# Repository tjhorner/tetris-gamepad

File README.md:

# Tetris Gamepad

These are the source files for an arcade-style gamepad designed for Tetris gameplay. Work in progress (things will break!)

**Disclaimer**: Tetris is a trademark of The Tetris Company, and I am not affiliated in any way with them. I'm just a fan of the game, and wanted to make this cool project for fun (and not profit). If you're a TTC lawyer and want me to rename this project, just let me know and I'll gladly do so. (No need to DMCA 😛)

## Directory Structure

- `src`: Source files for the firmware (licensed under MIT)
- `design`: PCB and enclosure design files (licensed under CC-BY-SA 4.0)
  - **Note:** The KiCad files may require you to install the [DigiKey library](https://forum.digikey.com/t/importing-the-digi-key-kicad-library-into-kicad-5-0-0/4075)

## Hardware

**License:** CC-BY-SA 4.0

This project is intended to be used with the [Adafruit HUZZAH32](https://www.adafruit.com/product/3405) board (mostly because that's what I had lying around), but with minor tweaks could be modified to use any ESP32 board, or even a raw ESP32 chip. The design is pretty simple; it just uses the GPIO pins in either `INPUT_PULLUP` mode (for the button inputs) or `OUTPUT` mode (for the button LEDs). Since it uses the `INPUT_PULLUP` mode, and the button LEDs have an inbuilt 200ohm resistor, no additional resistors are required.

If you want to build one yourself, here are the components you will need:

- 1x [Adafruit HUZZAH32](https://www.adafruit.com/product/3405)
- 8x [Arcade Button](https://www.adafruit.com/product/3491) (get creative with the colors!)
- 16x [Arcade Button Quick Connect Wire Pairs](https://www.adafruit.com/product/1152)
- 16x [B2B-XH-A JST Connector](https://www.digikey.com/en/products/detail/jst-sales-america-inc/B2B-XH-A-LF-SN/1651045)

You can find the KiCad files for the PCB design in the `design/pcb` directory, or if you want to quickly order some, here's a fancy button that will take you to the OSH Park page for the project:

## Enclosure

**License:** CC-BY-SA 4.0

The enclosure is a pretty simple box with fingers to assemble it, generated by [MakerCase](https://en.makercase.com/). There are holes in the top of the box that should fit the buttons snugly, along with some engravings near the buttons to indicate what they're for.

You can find the design files for the enclosure in the `design/enclosure` directory if you want to cut one out yourself.

## Firmware

**License:** MIT

The firmware development workflow is powered by [PlatformIO](https://platformio.org/), so you will need to get that set up if you want to modify or flash the firmware. All the dependencies are listed in the `platformio.ini` file so you shouldn't need to download anything manually.

### Operating Modes

The mode you are currently in will be indicated by how many times the startup animation loops (one cycle of the startup animation is all the LEDs turning on in order, then turning off).

- 1 time: gamepad mode
- 2 times: keyboard mode
- 3 times: Switch Pro Controller mode

You can switch between the modes by holding down a certain button during startup:

- HOLD: Switch to gamepad mode
- CCW: Switch to keyboard mode
- CW: Switch to Pro Controller mode

The default is gamepad mode. It will remember what mode you last selected on startup, so you don't need to hold the button down every time.

#### Gamepad Mode

In gamepad mode, the device will broadcast itself as a BLE gamepad. By default, the buttons are defined as such:

| **Physical Button** | **Virtual Button** |
|---------------------|--------------------|
| Hold                | Button 0           |
| CCW                 | Button 1           |
| CW                  | Button 2           |
| Left                | Button 3           |
| Right               | Button 4           |
| Hard Drop           | Button 5           |
| Soft Drop           | Button 6           |
| Zone                | Button 7           |

This does not follow a standard layout for e.g., an Xbox controller, so you will probably need to set up custom bindings in the game you are playing. You can also change the button assignments in the `modes/gamepad.h` file.

#### Keyboard Mode

In keyboard mode, the device will broadcast itself as a BLE keyboard. This mode is not as stable as gamepad or Pro Controller mode, so it should be used only as a backup method if those don't work.

The default bindings are:

| **Button** | **Key**     |
|------------|-------------|
| Hold       | Left Shift  |
| CCW        | Z           |
| CW         | X           |
| Left       | Left Arrow  |
| Right      | Right Arrow |
| Hard Drop  | Space       |
| Soft Drop  | Down Arrow  |
| Zone       | A           |

They follow normal the normal Guideline layout, so you should be fine with most games, but if you need to change them, you can do so in the `modes/keyboard.h` file.

#### Pro Controller Mode

Since the Switch does not support using generic Bluetooth gamepads, this is a special mode which imitates a Pro Controller.

**Note:** To use the gamepad with your Switch in Pro Controller mode, you will need to go to `Controllers > Change Grip/Order` every time you connect the controller. It's annoying, but I haven't figured out how to persist the pairing with the console.

The default bindings are:

| **Physical Button** | **Virtual Button** |
|---------------------|--------------------|
| Hold                | L                  |
| CCW                 | B                  |
| CW                  | A                  |
| Left                | D-Pad Left         |
| Right               | D-Pad Right        |
| Hard Drop           | D-Pad Up           |
| Soft Drop           | D-Pad Down         |
| Zone                | ZL                 |

Similar to the keyboard mode, these bindings also follow the Guideline layout, but can be changed in `modes/switch.h`.

### Configuration

If you want to modify which pins correspond to which buttons, you can do that in the `config.h` file. For convenience, `pins.h` defines a list of which JST connectors (labeled on the PCB) correspond to which GPIO pins (you can also modify this if need be).

You can also change which buttons you need to press to switch between modes.

There are a few other useful config options here as well; I'll document them eventually.

## Acknowledgements

Thanks to...

- The kind folks at [NYC Resistor](https://www.nycresistor.com/) for hosting their public craft nights, which opened up a bunch of resources and tools (namely, the laser cutter!) to me, helping make this project a reality
- The creator of [MakerCase](https://en.makercase.com/) for making laser cut boxes easy
- The creator of both the [ESP32 gamepad](https://github.com/lemmingDev/ESP32-BLE-Gamepad) and [ESP32 keyboard](https://github.com/T-vK/ESP32-BLE-Keyboard) libraries, which are basically the entire basis for the firmware
- The [BlueCubeMod](https://github.com/NathanReeves/BlueCubeMod) project, which is what the Pro Controller mode is largely based on

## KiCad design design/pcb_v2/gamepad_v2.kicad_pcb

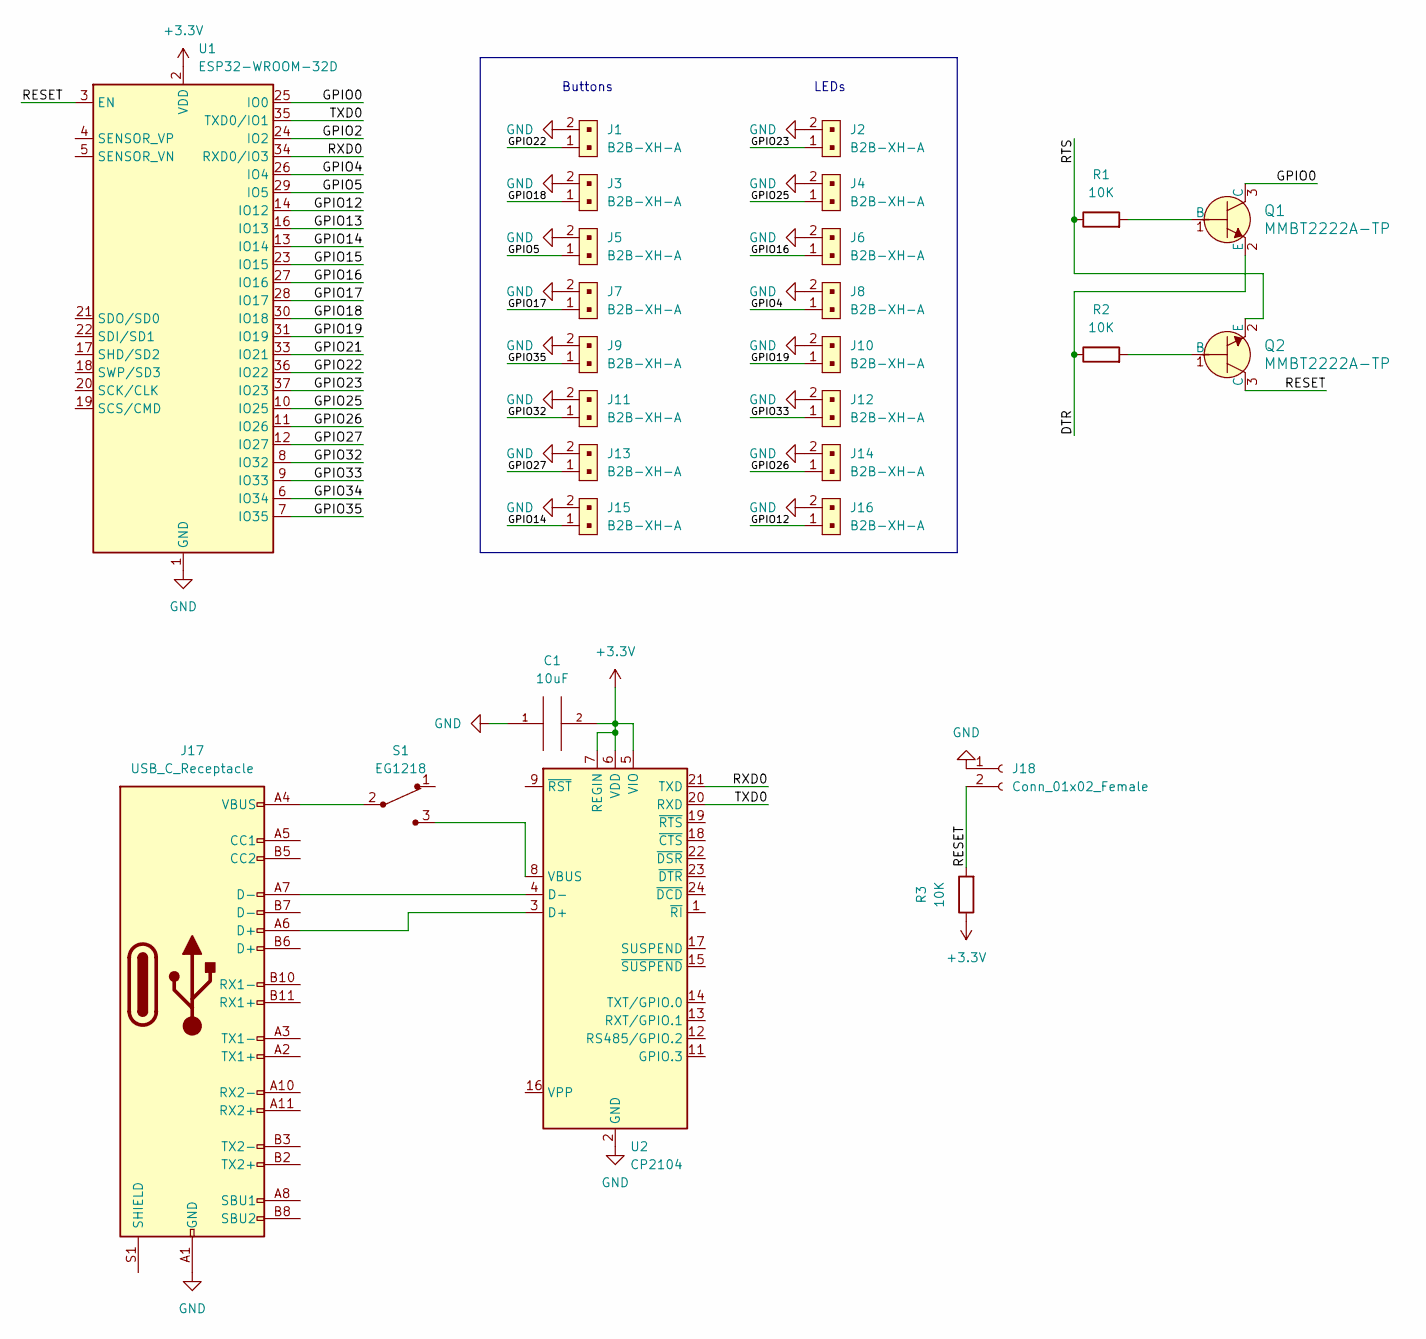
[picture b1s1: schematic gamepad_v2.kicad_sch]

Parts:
C1: 10uF; C_0603_1608Metric
J1, J2, J3, J4, J5, J6, J7, J8, J9, J10, J11, J12, J13, J14, J15, J16: B2B-XH-A; PinHeader_1x2_P2.5mm_Drill1.1mm; MPN B2B-XH-A(LF)(SN); Digi-Key_PN 455-2247-ND
J17: USB_C_Receptacle; USB-C_Female_12401X
J18: Conn_01x02_Female; PinHeader_1x02_P2.54mm_Vertical
Q1, Q2: MMBT2222A-TP; SOT-23-3; MPN MMBT2222A-TP; Digi-Key_PN MMBT2222ATPMSCT-ND
R1, R2, R3: 10K; R_0603_1608Metric_Pad0.98x0.95mm_HandSolder
S1: EG1218; Switch_Slide_11.6x4mm_EG1218; MPN EG1218; Digi-Key_PN EG1903-ND
U1: ESP32-WROOM-32D; ESP32-WROOM-32
U2: CP2104; QFN-24-1EP_4x4mm_P0.5mm_EP2.6x2.6mm

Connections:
+3V3: C1.2, R3.1, U1.2 (VDD), U2.5 (VIO), U2.6 (VDD), U2.7 (REGIN)
/DTR: Q1.2 (E), R2.1
/GPIO0: Q1.3 (C), U1.25 (IO0)
/GPIO2: U1.24 (IO2)
/GPIO4: J8.1, U1.26 (IO4)
/GPIO5: J5.1, U1.29 (IO5)
/GPIO12: J16.1, U1.14 (IO12)
/GPIO13: U1.16 (IO13)
/GPIO14: J15.1, U1.13 (IO14)
/GPIO15: U1.23 (IO15)
/GPIO16: J6.1, U1.27 (IO16)
/GPIO17: J7.1, U1.28 (IO17)
/GPIO18: J3.1, U1.30 (IO18)
/GPIO19: J10.1, U1.31 (IO19)
/GPIO21: U1.33 (IO21)
/GPIO22: J1.1, U1.36 (IO22)
/GPIO23: J2.1, U1.37 (IO23)
/GPIO25: J4.1, U1.10 (IO25)
/GPIO26: J14.1, U1.11 (IO26)
/GPIO27: J13.1, U1.12 (IO27)
/GPIO32: J11.1, U1.8 (IO32)
/GPIO33: J12.1, U1.9 (IO33)
/GPIO34: U1.6 (IO34)
/GPIO35: J9.1, U1.7 (IO35)
/RESET: J18.2, Q2.3 (C), R3.2, U1.3 (EN); also elsewhere on the board
/RTS: Q2.2 (E), R1.1
/RXD0: U1.34 (RXD0/IO3), U2.21 (TXD)
/TXD0: U1.35 (TXD0/IO1), U2.20 (RXD)
GND: C1.1, J1.2, J2.2, J3.2, J4.2, J5.2, J6.2, J7.2, J8.2, J9.2, J10.2, J11.2, J12.2, J13.2, J14.2, J15.2, J16.2, J17.A1 (GND), J17.A12 (GND), J17.B1 (GND), J17.B12 (GND), J18.1, U1.1 (GND), U1.15 (GND), U1.38 (GND), U1.39 (GND), U2.2 (GND), U2.25 (GND); also elsewhere on the board
unnamed 29: J17.A4 (VBUS), J17.A9 (VBUS), J17.B4 (VBUS), J17.B9 (VBUS), S1.2; also elsewhere on the board
unnamed: J17.A6 (D+), U2.3 (D+)
unnamed: J17.A7 (D-), U2.4 (D-)
unnamed: Q1.1 (B), R1.2
unnamed: Q2.1 (B), R2.2
unnamed 34: S1.3, U2.8 (VBUS); also elsewhere on the board

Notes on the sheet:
LEDs
Buttons

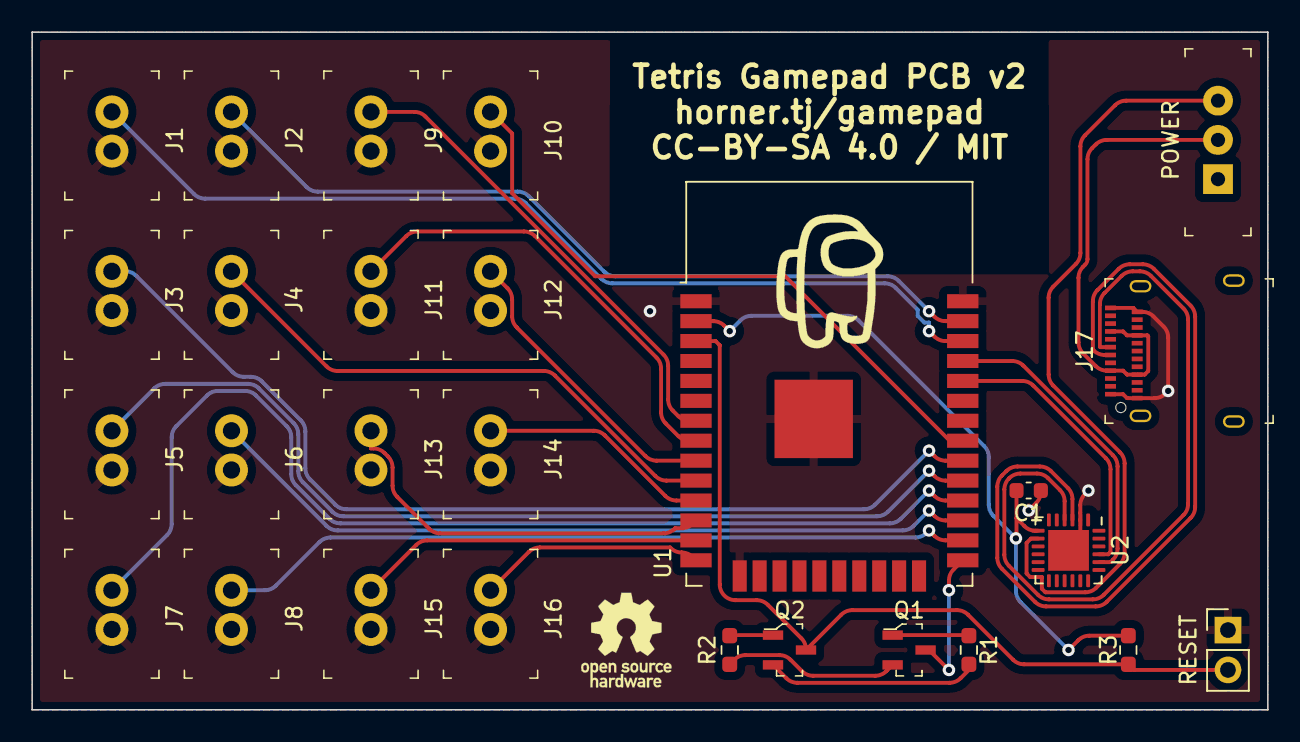
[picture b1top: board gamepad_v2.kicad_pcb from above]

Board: 2 copper layers, 78.7 x 43.2 mm, 28 parts (0 on the bottom side), 30 nets.

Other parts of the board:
POWER: EG1218; Switch_Slide_11.6x4mm_EG1218
RESET: Conn_01x02_Female; PinHeader_1x02_P2.54mm_Vertical
Ref**: Val**; amogus

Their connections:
/RESET: RESET.2; also elsewhere on the board
GND: RESET.1; also elsewhere on the board
unnamed 29: POWER.2; also elsewhere on the board
unnamed 34: POWER.3; also elsewhere on the board

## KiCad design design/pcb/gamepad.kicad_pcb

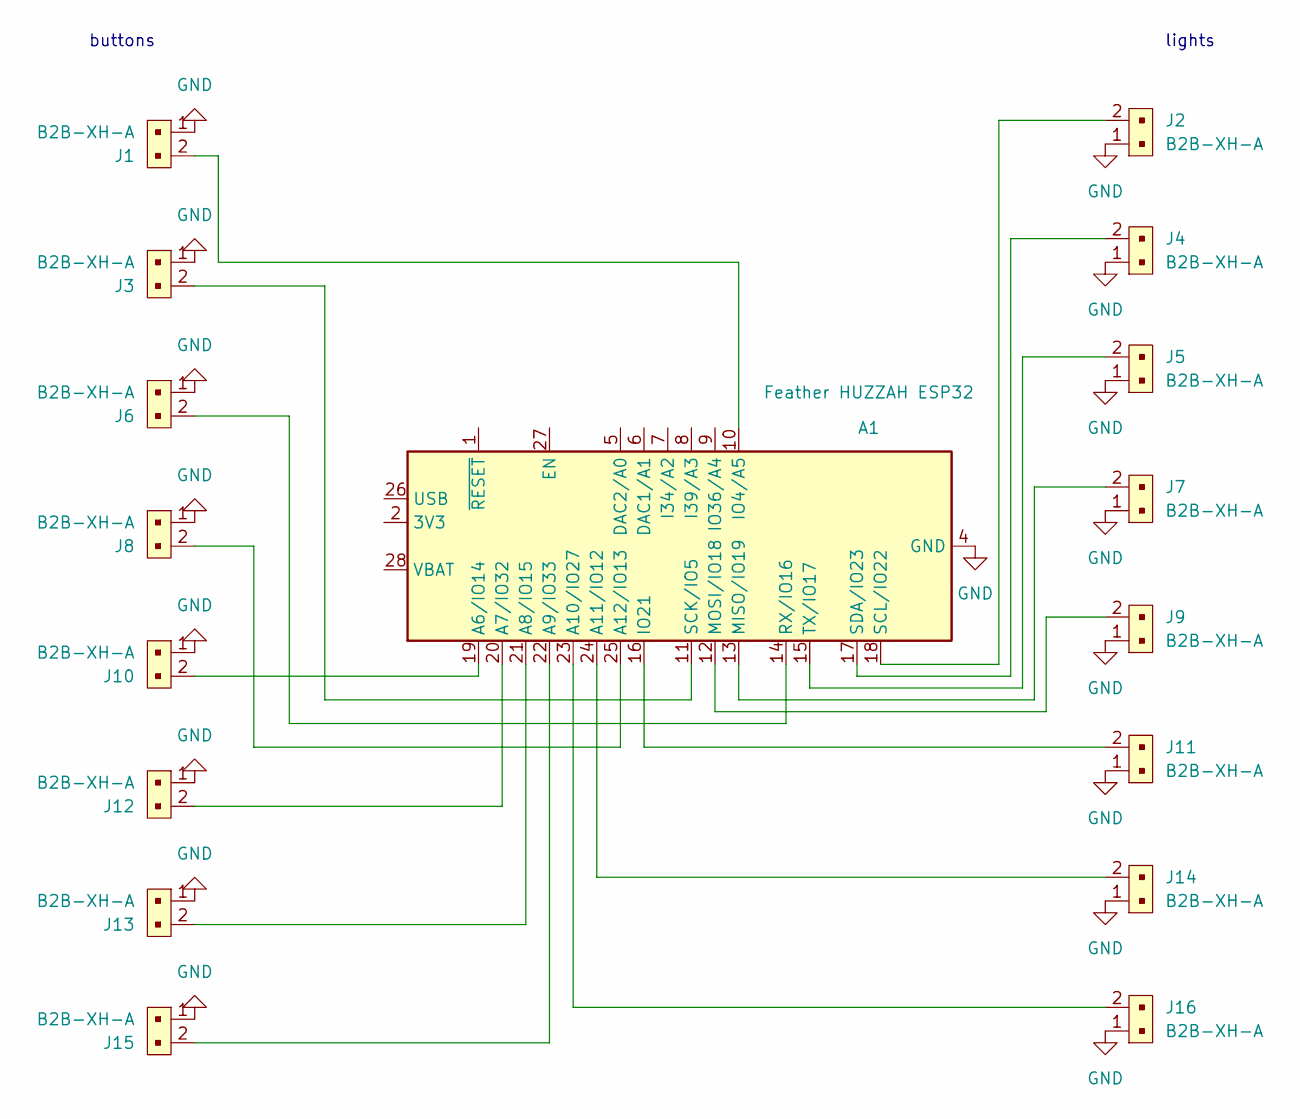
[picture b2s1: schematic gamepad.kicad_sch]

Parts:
A1: Feather HUZZAH ESP32; Adafruit_Feather
J1, J2, J3, J4, J5, J6, J7, J8, J9, J10, J11, J12, J13, J14, J15, J16: B2B-XH-A; PinHeader_1x2_P2.5mm_Drill1.1mm; MPN B2B-XH-A(LF)(SN); Digi-Key_PN 455-2247-ND

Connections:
GND: A1.4 (GND), J1.1, J2.1, J3.1, J4.1, J5.1, J6.1, J7.1, J8.1, J9.1, J10.1, J11.1, J12.1, J13.1, J14.1, J15.1, J16.1
unnamed: A1.10 (IO4/A5), J1.2
unnamed: A1.11 (SCK/IO5), J3.2
unnamed: A1.12 (MOSI/IO18), J9.2
unnamed: A1.13 (MISO/IO19), J7.2
unnamed: A1.14 (RX/IO16), J6.2
unnamed: A1.15 (TX/IO17), J5.2
unnamed: A1.16 (IO21), J11.2
unnamed: A1.17 (SDA/IO23), J4.2
unnamed: A1.18 (SCL/IO22), J2.2
unnamed: A1.19 (A6/IO14), J10.2
unnamed: A1.20 (A7/IO32), J12.2
unnamed: A1.21 (A8/IO15), J13.2
unnamed: A1.22 (A9/IO33), J15.2
unnamed: A1.23 (A10/IO27), J16.2
unnamed: A1.24 (A11/IO12), J14.2
unnamed: A1.25 (A12/IO13), J8.2

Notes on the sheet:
buttons
lights

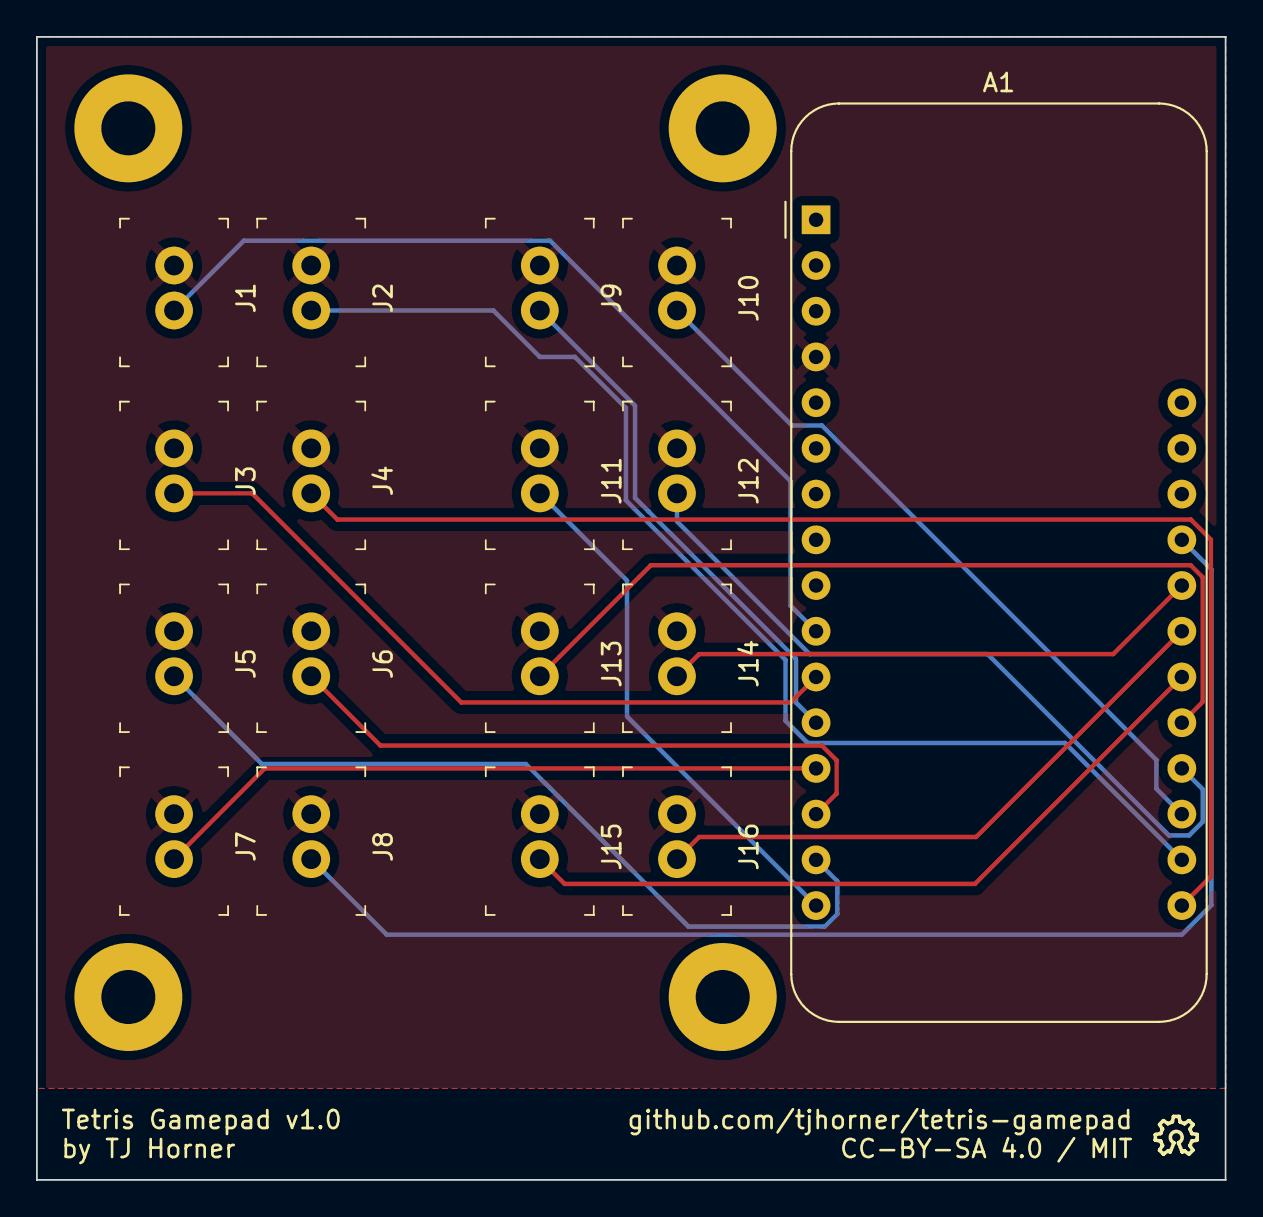
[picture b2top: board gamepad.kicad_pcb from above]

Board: 2 copper layers, 66.0 x 63.5 mm, 21 parts (0 on the bottom side), 17 nets.

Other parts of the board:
MH1, MH2, MH3, MH4: MountingHole_3mm_Pad

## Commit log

2022-02-22 stuff, wip
2022-03-01 some updates
2022-03-01 please macintosh operating system
2022-03-01 add a picture
2022-03-01 acknowledgements
2022-03-01 update traces
2022-03-01 firmware update, fix an oopsie in the pcb
2022-03-01 readme
2022-03-01 startup animation which indicates the mode
2022-03-02 readme enhancements, save mode across restarts
2022-03-02 more
2022-03-02 remove da notes
2022-03-02 comment
2022-03-02 remove some stuff
2022-03-02 switch pro controller kinda
2022-03-02 use unique MAC per mode
2022-03-03 working Switch mode
2022-03-03 note about switch mode
2022-03-03 switch to ESP-IDF entrypoint, stuff to make latency better
2022-03-03 more stuff
2022-03-03 doccs
2022-03-03 aaaaae
2022-03-03 re-enable LED stuffs
2022-03-04 switch away from interrupts, that appears to be faster
2022-03-04 remove dead code
2022-03-04 clean up pro controller code a bit
2022-03-04 change the thing
2022-03-04 attribution
2022-03-10 migrate logging to ESP logging library to keep things consistent
2022-03-10 initial stuff for PCB v2, which uses a raw ESP32-WROOM
2022-03-10 working on the pcb
2022-03-10 disclaimer
2022-03-10 fix pro controller mode (thanks git bisect)
2022-03-10 move gitignore up a directory
2022-03-11 fix broken link
2022-03-12 some pcb stuff
2022-03-12 more pcb stuff
2022-03-12 I think this is fine
2022-03-12 more pcb stuff 2
2022-03-12 change footprint location, add OSH logo

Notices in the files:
design/pcb/gamepad.kicad_pcb:
CC-BY-SA 4.0 / MIT
